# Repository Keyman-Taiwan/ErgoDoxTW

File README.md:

# ErgoDoxTW
Change was made based on [ErgoDone v1.5](https://github.com/ktec-hq/ErgoDone/commit/091d1d12327a9dc95b3b4be09c8e6d85ce0d4d30)  

## PCB Preview in KiCad

You can find a larger image in the preview folder.

`IMPORTANT`: v1.4 has been validated.

## Difference/Improvement with ErgoDone
1. Rollback to use Teensy 2.0 for main controller (same as ErgoDox)
2. Rollback to use MCP23018 for IO expander (same as ErgoDox)
3. USB Type-C connector (only support USB 2.0 due to Teensy 2.0)
4. Support to use Kailh / Gateron hot plug socket
5. Support to use SMD 1206 component for Resistor and Capacitor
6. Change TRRS socket to PJ-320A and PJ-320E, which is more easy to find and cheapper. (please check folder ref_data/3.5mm
)
7. **`ONLY`** support 76 keys due to component change and pcb layout change.

## Branch Description
* master & USB_C_DIP_RightHand: Teensy IC on Right hand (Compatible with ErgoDox-EZ Configurator)
* USB_C_DIP: Teensy IC on Left hand

## Software Requirement
* Kicad 5.1.4

## KiCad library used by ErgoDoxTW
* [ai03-2725/Type-C Connecter](https://github.com/ai03-2725/Type-C.pretty): HRO-TYPE-C-31-M-12
* [daprice/keyswitches](https://github.com/daprice/keyswitches.pretty): Kailh hotplug socket
* Some components in ErgoDone's library
* Some components in ErgoDox's library

## KiCad Plugin used by ErgoDoxTW
* [NilujePerchut/kicad_scripts](https://github.com/NilujePerchut/kicad_scripts): teardrop pluging

## 3D model for preview
* [Kailh Hotplug Socket](https://github.com/qmk/qmk_hardware/tree/master/components): from qmk @ github
* [Cherry MX switch](https://github.com/ConstantinoSchillebeeckx/cherry-mx-switch): from ConstantinoSchillebeeckx @ github
* [Cherry MX Stabilizer](https://grabcad.com/library/cherry-mx-stabilizer-mx-1): from GrabCad
* SMD Diode / Resistor / LED are built-in model in KiCad

## BOM List
|               Item               | Amount |                                                                Comment                                                               |
|:--------------------------------:|:------:|:------------------------------------------------------------------------------------------------------------------------------------:|
| PCB boards                       |    2   | One for each hand                                                                                                                    |
| Teensy 2.0                       |    1   | Maion controller                                                                                                                     |
| MCP23018                         |    1   | I/O expander, Please choose DIP type                                                                                                 |
| 2.54mm Header Pins               |   24   | Unless pre-installed on the teensy board                                                                                             |
| Key switches                     |   76   | Compatible with Cherry MX is fine.                                                                                                   |
| Key Switch Hotplug Socket        |   76   | Kailh or Gateron. This is Optional                                                                                                   |
| Key Caps                         |   76   |                                                                                                                                      |
| 1N4148 diodes                    |   76   | SOD-123 package (SMD Type) or DO-35 (0.3” pitch) (Through-Hole Type)                                                                 |
| 3mm T1 LED                       |    3   |                                                                                                                                      |
| 220 Ω Resistor                   |    3   | Through-Hole Type Or 1206 SMD type (Red, Red, Brown)                                                                                 |
| 2.2k Ω Resistor                  |    2   | Through-Hole Type Or 1206 SMD type (Red, Red, Red)                                                                                   |
| 5.1k Ω Resistor                  |    2   | Through-Hole Type Or 1206 SMD type (Green, Brown, Red)                                                                               |
| 0.1μ F Capacitor                 |    1   | ceramic capacitor (marked “104” for 10*104 picofarad, or 100nF), also supported 1206 smd type. Not strictly necessary but suggested. |
| USB Type C connector             |    1   | 林躍電子 UB228-F16S4BR-A_DIP Or 浙富電子 16P 雙排 DIP                                                                                |
| USB mini B plug with short cable |    1   | Such as H2955. Use for connect type c connector and teensy board                                                                     |
| USB Type C Cable                 |    1   | A male to male cable, for connect keyboard to PC. (A to C) or (C to C) depend on your device.                                        |
| 3.5mm TRRS socket                |    2   | PJ-320A or PJ-320E                                                                                                                   |
| 3.5mm TRRS Cable                 |    1   | A male to male cable, for connect two pcbs.                                                                                          |
| ErgoDoxTW Keyboard case          |    1   | Acrylic Case                                                                                                                         |

# Lisence
GPL v3

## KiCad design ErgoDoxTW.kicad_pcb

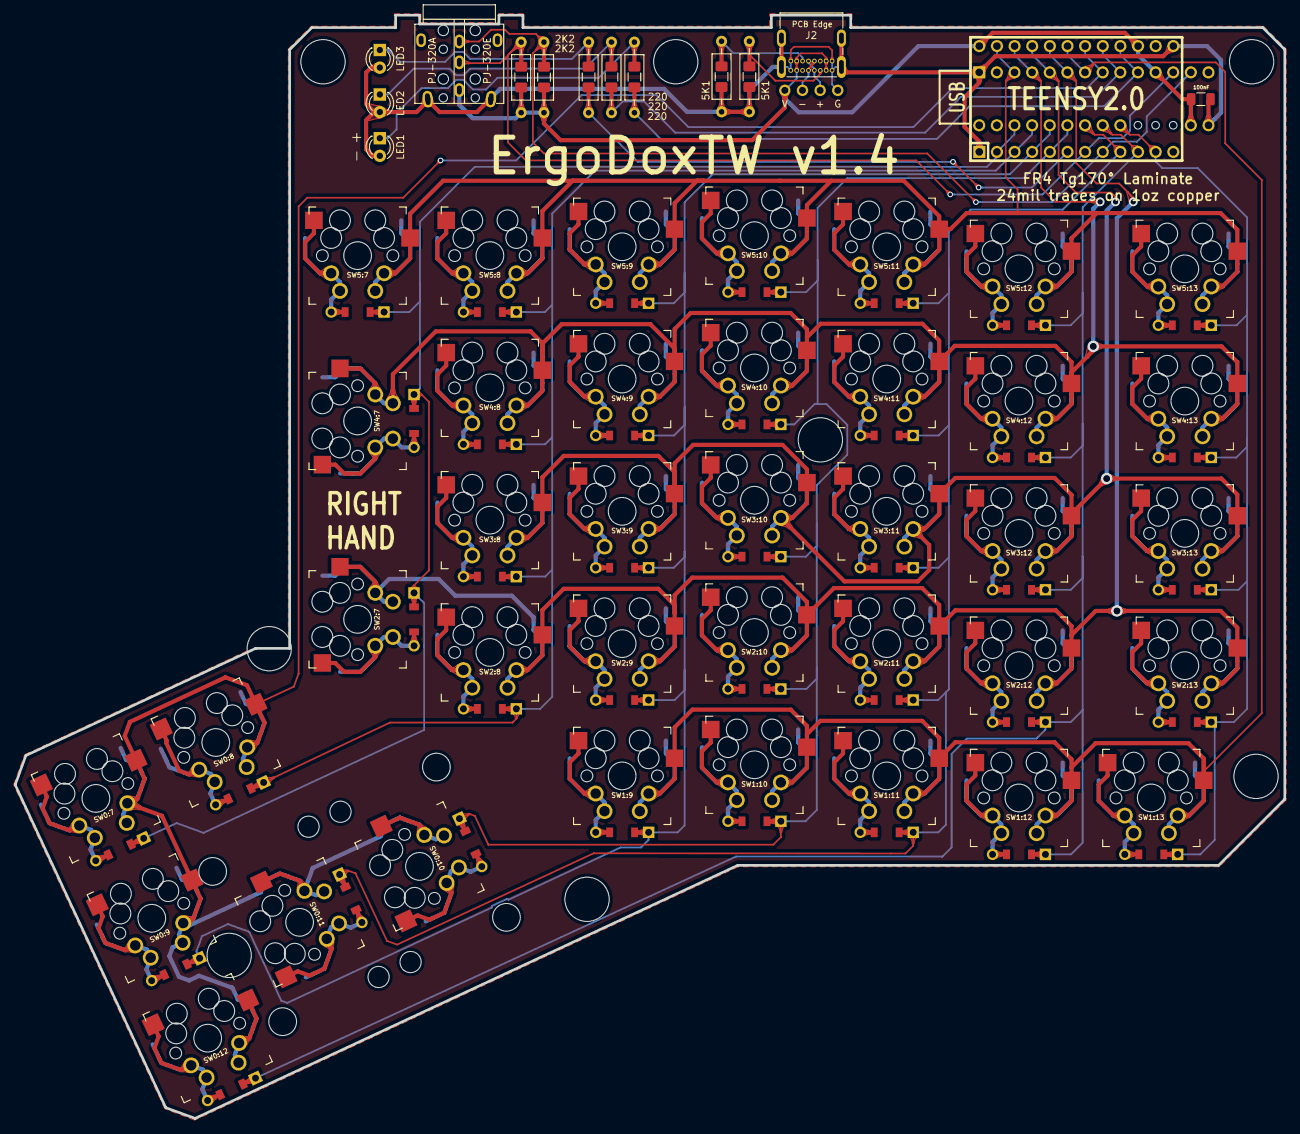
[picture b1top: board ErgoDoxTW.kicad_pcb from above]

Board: 2 copper layers, 182.8 x 158.9 mm, 63 parts (1 on the bottom side), 65 nets.

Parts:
100nF: 100nF; C_1206_3216Metric
J1: 3.5mm; PJ-320A_and_320E-Dual
J2: USB_C; TYPE_C_UB228-F16S4BR-A_DIP
LED1: LEDa; LED_D3.0mm_Clear
LED2: LEDb; LED_D3.0mm_Clear
LED3: LEDc; LED_D3.0mm_Clear
R1, R2: 2K2; R_Axial_DIN0207_L6.3mm_D2.5mm_P10.16mm_Horizontal
R3, R6: 2K2; R_1206_3216Metric_Pad1.42x1.75mm_HandSolder
R4, R5: 5K1; R_Axial_DIN0207_L6.3mm_D2.5mm_P10.16mm_Horizontal
R7, R8: 5K1; R_1206_3216Metric_Pad1.42x1.75mm_HandSolder
RA1: LEDa; R_Axial_DIN0207_L6.3mm_D2.5mm_P10.16mm_Horizontal
RA2: 220; R_1206_3216Metric_Pad1.42x1.75mm_HandSolder
RB1: LEDb; R_Axial_DIN0207_L6.3mm_D2.5mm_P10.16mm_Horizontal
RB2: 220; R_1206_3216Metric_Pad1.42x1.75mm_HandSolder
RC1: LEDc; R_Axial_DIN0207_L6.3mm_D2.5mm_P10.16mm_Horizontal
RC2: 220; R_1206_3216Metric_Pad1.42x1.75mm_HandSolder
S1, S2: STAB200; STAB_PCB940
S3: MEHCINAL; ErgoDOXmech
SW0:7: SW0:6; Kailh_socket_diode_smd
SW0:8: SW0:5; Kailh_socket_diode_smd
SW0:9: SW0:4; Kailh_socket_diode_smd
SW0:10: SW0:3; Kailh_socket_diode_smd
SW0:11: SW0:2; Kailh_socket_diode_smd
SW0:12: SW0:1; Kailh_socket_diode_smd
SW1:9: SW1:4; Kailh_socket_diode_smd
SW1:10: SW1:3; Kailh_socket_diode_smd
SW1:11: SW1:2; Kailh_socket_diode_smd
SW1:12: SW1:1; Kailh_socket_diode_smd
SW1:13: SW1:0; Kailh_socket_diode_smd
SW2:7: SW2:6; Kailh_socket_diode_smd
SW2:8: SW2:5; Kailh_socket_diode_smd
SW2:9: SW2:4; Kailh_socket_diode_smd
SW2:10: SW2:3; Kailh_socket_diode_smd
SW2:11: SW2:2; Kailh_socket_diode_smd
SW2:12: SW2:1; Kailh_socket_diode_smd
SW2:13: SW2:0; Kailh_socket_diode_smd
SW3:8: SW3:5; Kailh_socket_diode_smd
SW3:9: SW3:4; Kailh_socket_diode_smd
SW3:10: SW3:3; Kailh_socket_diode_smd
SW3:11: SW3:2; Kailh_socket_diode_smd
SW3:12: SW3:1; Kailh_socket_diode_smd
SW3:13: SW3:0; Kailh_socket_diode_smd
SW4:7: SW4:6; Kailh_socket_diode_smd
SW4:8: SW4:5; Kailh_socket_diode_smd
SW4:9: SW4:4; Kailh_socket_diode_smd
SW4:10: SW4:3; Kailh_socket_diode_smd
SW4:11: SW4:2; Kailh_socket_diode_smd
SW4:12: SW4:1; Kailh_socket_diode_smd
SW4:13: SW4:0; Kailh_socket_diode_smd
SW5:7: SW5:6; Kailh_socket_diode_smd
SW5:8: SW5:5; Kailh_socket_diode_smd
SW5:9: SW5:4; Kailh_socket_diode_smd
SW5:10: SW5:3; Kailh_socket_diode_smd
SW5:11: SW5:2; Kailh_socket_diode_smd
SW5:12: SW5:1; Kailh_socket_diode_smd
SW5:13: SW5:0; Kailh_socket_diode_smd
U2: MCP23018; DIP28_300
U4: TEENSY2.0; TEENSY_2.0_WO_RESET

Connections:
/COL0: SW1:13.4, SW2:13.4, SW3:13.4, SW4:13.4, SW5:13.4, U2.20, U4.11
/COL1: SW0:12.4, SW1:12.4, SW2:12.4, SW3:12.4, SW4:12.4, SW5:12.4, U2.21, U4.10
/COL4: SW0:9.4, SW1:9.4, SW2:9.4, SW3:9.4, SW4:9.4, SW5:9.4, U2.24, U4.4
/COL5: SW0:8.4, SW2:8.4, SW3:8.4, SW4:8.4, SW5:8.4, U2.25, U4.3
/COL6: SW0:7.4, SW2:7.4, SW4:7.4, SW5:7.4, U2.26, U4.2
/COL10: SW0:10.4, SW1:10.4, SW2:10.4, SW3:10.4, SW4:10.4, SW5:10.4, U2.23, U4.5
/COL11: SW0:11.4, SW1:11.4, SW2:11.4, SW3:11.4, SW4:11.4, SW5:11.4, U2.22, U4.9
/LED_A: RA1.1, RA2.1, U2.10, U4.21
/LED_B: RB1.1, RB2.1, U2.9, U4.22
/LED_C: RC1.1, RC2.1, U4.6
/ROW0: SW0:7.1, SW0:8.1, SW0:9.1, SW0:10.1, SW0:11.1, SW0:12.1, U2.8, U4.23
/ROW1: SW1:9.1, SW1:10.1, SW1:11.1, SW1:12.1, SW1:13.1, U2.7, U4.24
/ROW2: SW2:7.1, SW2:8.1, SW2:9.1, SW2:10.1, SW2:11.1, SW2:12.1, SW2:13.1, U2.6, U4.25
/ROW3: SW3:8.1, SW3:9.1, SW3:10.1, SW3:11.1, SW3:12.1, SW3:13.1, U2.5, U4.26
/ROW4: SW4:7.1, SW4:8.1, SW4:9.1, SW4:10.1, SW4:11.1, SW4:12.1, SW4:13.1, U2.4, U4.27
/ROW5: SW5:7.1, SW5:8.1, SW5:9.1, SW5:10.1, SW5:11.1, SW5:12.1, SW5:13.1, U2.3, U4.28
/SCLM: J1.3, R2.2, R6.2, U2.12, U4.7
/SDAM: J1.2, R1.2, R3.2, U2.13, U4.8
GND: 100nF.2, J1.5, J2.A1, J2.A12, J2.B1, J2.B12, J2.S1, LED1.2, LED2.2, LED3.2, R4.2, R5.2, R7.2, R8.2, U2.1, U2.15, U4.1, U4.18
unnamed: J2.A5, R5.1, R7.1
unnamed: J2.A6, J2.B6
unnamed: J2.A7, J2.B7
unnamed: J2.B5, R4.1, R8.1
unnamed: LED1.1, RA1.2, RA2.2
unnamed: LED2.1, RB1.2, RB2.2
unnamed: LED3.1, RC1.2, RC2.2
unnamed: SW0:7.2, SW0:7.3
unnamed: SW0:8.2, SW0:8.3
unnamed: SW0:9.2, SW0:9.3
unnamed: SW0:10.2, SW0:10.3
unnamed: SW0:11.2, SW0:11.3
unnamed: SW0:12.2, SW0:12.3
unnamed: SW1:9.2, SW1:9.3
unnamed: SW1:10.2, SW1:10.3
unnamed: SW1:11.2, SW1:11.3
unnamed: SW1:12.2, SW1:12.3
unnamed: SW1:13.2, SW1:13.3
unnamed: SW2:7.2, SW2:7.3
unnamed: SW2:8.2, SW2:8.3
unnamed: SW2:9.2, SW2:9.3
unnamed: SW2:10.2, SW2:10.3
unnamed: SW2:11.2, SW2:11.3
unnamed: SW2:12.2, SW2:12.3
unnamed: SW2:13.2, SW2:13.3
unnamed: SW3:8.2, SW3:8.3
unnamed: SW3:9.2, SW3:9.3
unnamed: SW3:10.2, SW3:10.3
unnamed: SW3:11.2, SW3:11.3
unnamed: SW3:12.2, SW3:12.3
unnamed: SW3:13.2, SW3:13.3
unnamed: SW4:7.2, SW4:7.3
unnamed: SW4:8.2, SW4:8.3
unnamed: SW4:9.2, SW4:9.3
unnamed: SW4:10.2, SW4:10.3
unnamed: SW4:11.2, SW4:11.3
unnamed: SW4:12.2, SW4:12.3
unnamed: SW4:13.2, SW4:13.3
unnamed: SW5:7.2, SW5:7.3
unnamed: SW5:8.2, SW5:8.3
unnamed: SW5:9.2, SW5:9.3
unnamed: SW5:10.2, SW5:10.3
unnamed: SW5:11.2, SW5:11.3
unnamed: SW5:12.2, SW5:12.3
unnamed: SW5:13.2, SW5:13.3
VCC: 100nF.1, J1.4, J2.A4, J2.A9, J2.B4, J2.B9, R1.1, R2.1, R3.1, R6.1, U2.11, U2.16, U4.20, U4.29

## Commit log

2019-09-11 add gitignore
2019-09-11 v1.0
2019-09-11 Add software reqirement
2019-09-12 update v1.0
    1. Change USB VCC trace to 0.609 mm
    2. Make all via larger
    3. reroute the trace in thumb area
    4. add some pcb text
    5. update README.md
2019-09-12 Add pcb preview image to README.md
2019-09-13 Add keypart description
2019-09-17 update to v1.2
    1. change 3.5mm audio socket component to PJ-320A (pin on right side)
    and PJ-320L (pin on left side)
    2. change key switch layout
    3. change
    trace to 0.609 mm for key switch (due to above)
    4. fix some typo
2019-09-18 update v1.2.1
    Main change :
    1. fix 3.5mm audio jack position
    Minor change:
    1. add key_switch / stabilizer 3d models for preview
    2. add full pcb preview image
2019-09-18 fix readme
2019-09-19 update v1.3
    support PJ-320E 3.5mm audio jack
2019-09-21 update keypart desc in README
2019-09-21 change type c connector from smd to dip
2019-09-21 update lib from USB_C_DIP branch
2019-09-21 pcb: fix usb vcc and gnd connection
2019-09-21 add reference data
2019-09-21 ref_data: add pj-320e
2019-09-22 update pcb edge for 3.5mm and type c
2019-09-24 add v1.3b layout
    change IC layout as ErgoDox, Right Hand is TOP side (main)
2019-09-24 rename ErgoDoxTW to ErgoDoneTW
2019-09-24 update pcb_preview link
2019-09-24 update smd cap position to avoid conflict with mcp23018
2019-09-24 update v1.4
    change led / resistor position due to add new drill hole from ErgoDox
    for a better support with cases.
2019-09-30 update v1.4 (resync and clean-up)
    1. rename project to ErgoDoxTW
    2. fix silk print on PJ-320A_and_PJ-320E kicad module
    3. remove 3d models preview for unused components
    3. remove unused components and 3d models step files
2019-09-30 update v1.4 from branch USB_C_DIP_RightHand
    1. rename project to ErgoDoxTW
    2. Drill hole is compatible with ErgoDox
    3. fix silk print on PJ-320A_and_PJ-320E kicad module
    4. remove 3d models preview for unused components
    5. remove unused components and 3d models step files
2019-10-02 update Readme and v1.4 preview image
2019-10-02 fix type in readme
2019-10-17 v1.4 formal release
    update TRRS position and silksprint
2019-10-17 Update readme for v1.4 formal release
2020-01-12 Update LICENSE
